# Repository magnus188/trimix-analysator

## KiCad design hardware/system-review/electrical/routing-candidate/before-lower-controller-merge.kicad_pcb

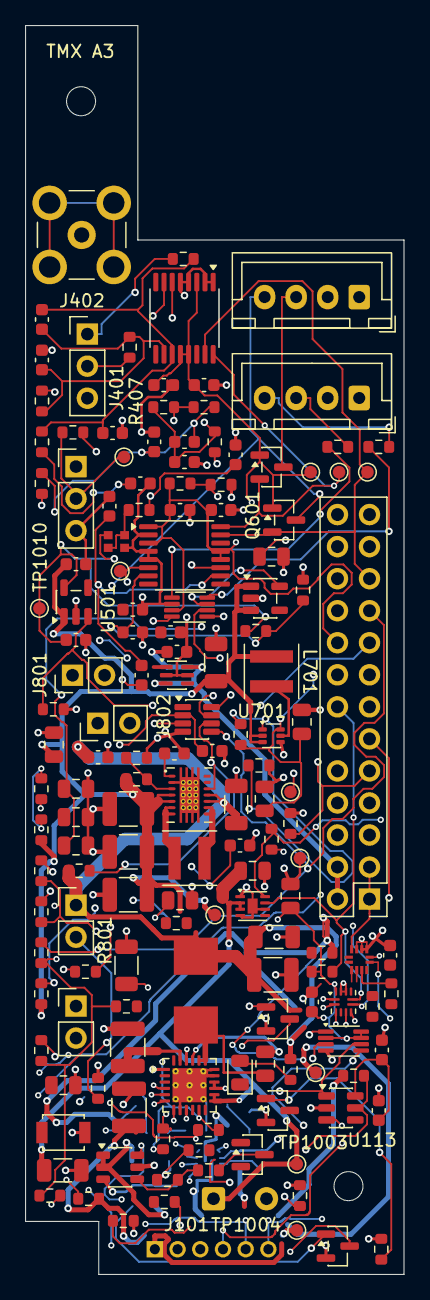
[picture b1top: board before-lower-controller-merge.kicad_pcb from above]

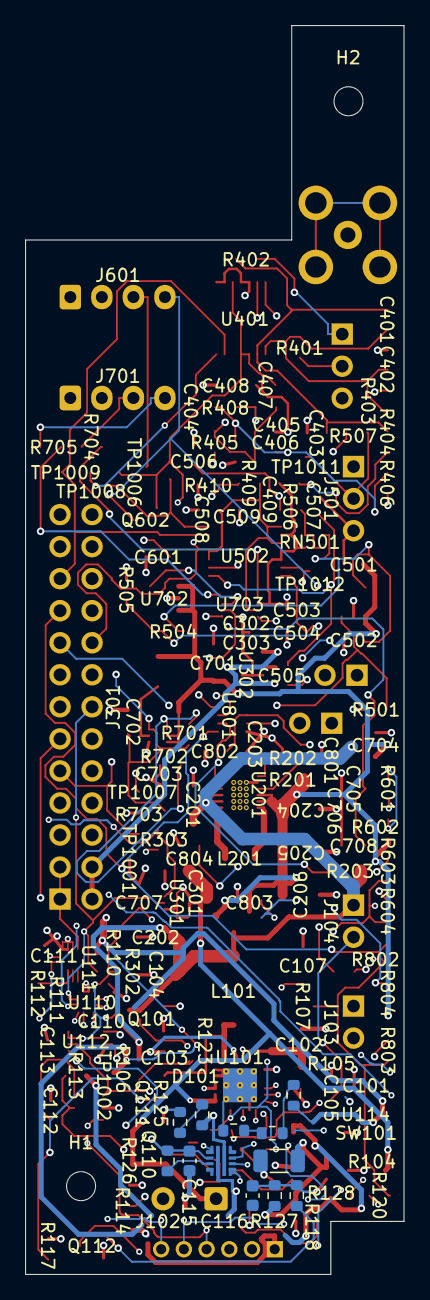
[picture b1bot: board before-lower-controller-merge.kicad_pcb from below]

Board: 4 copper layers, 30.0 x 99.0 mm, 169 parts (12 on the bottom side), 87 nets.

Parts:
C101, C601, C704, C705: 1u / 25V X7R / 10%; C_0805_2012Metric
C102, C104, C105, C204, C205, C206: 22u / 16V X7R / 20%; C_1210_3225Metric
C103: 47n / 50V X7R / 10%; C_0805_2012Metric
C106, C107, C201, C202, C701: 22u / 25V X5R / 20%; C_1206_3216Metric
C110, C111, C112, C113, C203, C407, C504, C508, C801, C802: 100n / 50V X7R / 10%; C_0603_1608Metric
C114: 4.7u / 25V X7R / 10%; C_1206_3216Metric
C115: 100n / 50V X7R; C_0603_1608Metric
C116: 3.3n / 50V C0G / 5%; C_0603_1608Metric
C301, C707, C708: 100n / 50V X7R / 10%; C_0805_2012Metric
C302, C303, C501, C502: 4.7u / 16V X5R / 10%; C_0603_1608Metric
C401, C404, C408, C409, C505, C509, C804: 1u / 16V X7R / 10%; C_0603_1608Metric
C402, C403, C405, C406, C506, C507: 10n / 50V X7R / 10%; C_0603_1608Metric
C503: 10n / 50V X7R / 10% / DNP; C_0603_1608Metric
C702, C703: 22u / 16V X5R / 20%; C_0805_2012Metric
C706: 10n / 50V X7R / 10% / DNP; C_0805_2012Metric
C803: 33n / 50V X7R / 10%; C_0805_2012Metric
D101: CHARGE (red); LED_0805_2012Metric
H1, H2: M2 NPTH 2.30; Mechanical_M2_NPTH_2.30mm
J101: USB HARNESS: 5V/GND/CC1/CC2/D+/D-; USB_Harness_6P_P1.8mm
J102: PACK PIGTAIL; Battery_Pigtail_2x22AWG_P4.2_D1.00_Pad1.85
J103: PACK NTC: 103AT-2; PinHeader_1x02_P2.54mm_Vertical
J104: ARM: OPEN; PinHeader_1x02_P2.54mm_Vertical
J301: GUITION JP1 / 2x13; Samtec_HTSW-113-07-L-D-007_P2.54mm_Key7
J401: AO2 / 3-pin cable; PinHeader_1x03_P2.54mm_Vertical
J402: SMB male-centre / Amphenol142138; SMB_Amphenol_142138
J501: MD62 cable / <=30 cm; PinHeader_1x03_P2.54mm_Vertical
J601: BME280 harness; JST_XH_B4B-XH-A_1x04_P2.50mm_Vertical
J701: ZE07-CO harness; JST_XH_B4B-XH-A_1x04_P2.50mm_Vertical
J801: POWER BUTTON / 1NO; PinHeader_1x02_P2.54mm_Vertical
J802: BUTTON LED +/-; PinHeader_1x02_P2.54mm_Vertical
L101: 1u / 74437349010; L_Wurth_74437349010_7050
L201: 1.5u / XGL4030-152MEC; L_Coilcraft_XGL4030
L701: 1u / XGL4020-102MEC; L_Coilcraft_XGL4020
Q101: 2N7002; SOT-23
Q110, Q111, Q112: DMN2056U-7; SOT-23
Q601, Q602: BSS138; SOT-23
R101: 5.23k 1%; R_0603_1608Metric
R102: 30.1k 1%; R_0603_1608Metric
R103: 300R / 1% / supported ILIM range; R_0603_1608Metric
R104, R105, R203, R501, R703, R803: 100k; R_0603_1608Metric
R106: 2.2k; R_0603_1608Metric
R107, R301, R802: 10k; R_0603_1608Metric
R110: 887k / 1%; R_0603_1608Metric
R111: 33k / 1%; R_0603_1608Metric
R112, R115, R120, R127: 10k / 1%; R_0603_1608Metric
R113: 97.6k / 0.1%; R_0603_1608Metric
R114, R409, R410, R504, R505: 10k / 0.1%; R_0603_1608Metric
R116: 1k / 0.1%; R_0603_1608Metric
R117, R118, R128: 100k / 1%; R_0603_1608Metric
R119: 19.2k / 0.1%; R_0603_1608Metric
R121: 34k / 0.1% / 10ppm; R_0603_1608Metric
R122: 649R / 0.1% / 10ppm; R_0603_1608Metric
R123: 10k / 0.1% / 10ppm; R_0603_1608Metric
R124: 21.5k / 0.1% / 25ppm; R_0603_1608Metric
R125: 10k / 0.1% / 25ppm; R_0603_1608Metric
R126: 1.65k / 0.1%; R_0603_1608Metric
R201: 1.62M 1%; R_0603_1608Metric
R202: 180k 1%; R_0603_1608Metric
R302, R303: 4.7k / FIT; R_0603_1608Metric
R401, R402, R405, R406: 100R / 0.1%; R_0603_1608Metric
R403, R404, R407, R408: 1M / 1%; R_0603_1608Metric
R506, R507: 680R / 0.1%; R_0603_1608Metric
R601: 0R / fit: 3.3 V; R_0603_1608Metric
R602: 0R / DNP: 5 V option; R_0603_1608Metric
R603, R604: 4.7k / DNP; R_0603_1608Metric
R701: 787k / 0.1%; R_0603_1608Metric
R702: 100k / 0.1%; R_0603_1608Metric
R704, R705: 100R; R_0603_1608Metric
R801: 5.1k; R_0603_1608Metric
R804: 1k / DNP; R_0603_1608Metric
RN501: 2x2k / 1:1 matched; Vishay_ACAS0606_AT_IEC
SW101: BQ service wake / B3U-1000P; SW_SPST_B3U-1000P
TP1001: GND; TestPoint_Pad_D1.0mm
TP1002: USB_5V; TestPoint_Pad_D1.0mm
TP1003: PACK_P; TestPoint_Pad_D1.0mm
TP1004: VSYS; TestPoint_Pad_D1.0mm
TP1005: VOUT_5V; TestPoint_Pad_D1.0mm
TP1006: HOST_3V3; TestPoint_Pad_D1.0mm
TP1007: POWER_EN; TestPoint_Pad_D1.0mm
TP1008: I2C_SCL; TestPoint_Pad_D1.0mm
TP1009: I2C_SDA; TestPoint_Pad_D1.0mm
TP1010: HE_3V0; TestPoint_Pad_D1.0mm
TP1011: HE_SENSE; TestPoint_Pad_D1.0mm
TP1012: O2_VMID; TestPoint_Pad_D1.0mm
U101: BQ25895RTWR; Texas_RTW_WQFN-24-1EP_4x4mm_P0.5mm_EP2.7x2.7mm_ThermalVias
U110: TUSB320LAIRWBR; Texas_X2QFN-12_1.6x1.6mm_P0.4mm
U111: PI3USB9201ZTAEX; PI3USB9201_UQFN2020_12_TypeC
U112: SN74AUP1G74DCUR; VSSOP-8_2.3x2mm_P0.5mm
U113: TPS3808G01DBVR; SOT-23-6
U114: TPS22950CQDDCRQ1; TI_DDC0006A
U115: TPS259470ARPWR; TI_RPW0010A
U201: TPS63020DSJR; TI_DSJ_14
U301: MAX17048G+; TDFN-8-1EP_2x2mm_P0.5mm_EP0.8x1.2mm
U302: LM66100DCKR; SOT-363_SC-70-6
U401, U502: ADS122C04IPWR; TSSOP-16_4.4x5mm_P0.65mm
U501, U702: TPS7A2030PDBVR; SOT-23-5
U701: TPS61023DRLR; SOT-563
U703: TXU0202DCUR; TI_DCU8_CompactSilk
U801: LTC2954CTS8-1; TSOT-23-8

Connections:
/01 CHARGING + BATTERY/BQ_BTST: C103.2, U101.21 (BTST)
/01 CHARGING + BATTERY/BQ_PMID: C102.1, U101.23 (PMID)
/01 CHARGING + BATTERY/BQ_QON_N: SW101.1, U101.12 (~QON)
/01 CHARGING + BATTERY/BQ_REGN: C107.1, R101.1, U101.22 (REGN)
/01 CHARGING + BATTERY/BQ_SW: C103.1, L101.1, U101.19 (SW), U101.20 (SW)
/01 CHARGING + BATTERY/CHG_CE_N: Q101.3 (D), R104.2, U101.9 (~CE)
/01 CHARGING + BATTERY/CHG_STAT_N: D101.1 (K), U101.4 (STAT)
/01 CHARGING + BATTERY/PACK_TS: J103.1, R101.2, R102.1, U101.11 (TS)
/02 SWITCHED 5 V/TPS_FB: R201.2, R202.1, U201.3 (FB)
/02 SWITCHED 5 V/TPS_VINA: C203.1, U201.1 (VINA)
BME_SCL: J601.3 (SCL), Q601.3 (D), R603.2
BME_SDA: J601.4 (SDA), Q602.3 (D), R604.2
BME_VIN: C601.1, J601.1 (VIN), R601.2, R602.2, R603.1, R604.1
BQ_ILIM: R103.1, U101.10 (ILIM)
BUTTON_LED_A: J802.1, R804.2
CHARGE_ARM: J104.2 (B), Q101.1 (G), R105.1
CHG_INT_N: J301.13, Q112.3 (D), R107.2, U101.7 (~INT)
CO_5V28: C702.1, C703.1, J701.1 (5.28V), R701.1, U701.6 (VOUT)
CO_FB: R701.2, R702.1, U701.1 (FB)
CO_LOGIC_3V0: C705.1, C708.1, U702.5 (OUT), U703.7 (VCCB)
CO_RX_3V0: R705.1, U703.8 (B1Y)
CO_RX_CABLE: J701.4 (CO_RX), R705.2
CO_SW: L701.2, U701.5 (SW)
CO_TX_3V0: R704.1, U703.1 (B2)
CO_TX_CABLE: J701.3 (CO_TX), R704.2
CO_UART_EN: J301.9, R703.1, U703.6 (OE)
CO_UART_RX: J301.10, U703.4 (A2Y)
CO_UART_TX: J301.12, U703.5 (A1)
GAUGE_ALERT_N: R301.2, U301.5 (ALRT)
GND: C101.2, C102.2, C104.2, C105.2, C106.2, C107.2, C110.2, C111.2, C112.2, C113.2, C114.2, C115.2, C116.2, C201.2, C202.2, C203.2, C204.2, C205.2, C206.2, C301.2, C302.2, C303.2, C402.2, C403.2, C405.2, C406.2, C407.2, C408.2, C409.2, C501.2, C502.2, C503.2, C504.2, C506.2, C507.2, C508.2, C509.2, C601.2, C701.2, C702.2, C703.2, C704.2, C705.2, C706.2, C707.2, C708.2, C801.2, C802.2, C803.2, C804.2, J101.2, J102.2, J103.2, J301.5, J301.6, J301.16, J501.3, J601.2 (GND), J701.2 (GND), J801.2, J802.2, Q101.2 (S), Q111.2 (S), Q112.2 (S), R102.2, R103.2, R105.2, R114.2, R117.2, R118.2, R119.2, R123.2, R125.2, R126.2, R127.2, R128.2, R202.2, R410.2, R501.2, R505.2, R702.2, R703.2, RN501.3 (R2.2), SW101.2, TP1001.1 (1_1), U101.8 (OTG), U101.17 (PGND), U101.18 (PGND), U101.25 (PGND), U110.3 (PORT), U110.5 (ADDR), U110.10 (GND), U110.11 (EN_N), U111.9 (GND), U111.10 (ADDR), U111.11 (ENB), U112.4 (GND), U113.2 (GND), U114.3 (GND), U115.8 (GND), U201.2 (GND), U201.15 (PGND/EP), U301.1 (CTG), U301.4 (GND), U301.6 (QSTRT), U301.9 (EP), U302.2 (GND), U302.5 (ST), U401.1 (A0), U401.2 (A1), U401.4 (DGND), U401.5 (AVSS), U501.2 (GND), U502.2 (A1), U502.4 (DGND), U502.5 (AVSS), U701.4 (GND), U702.2 (GND), U703.2 (GND), U801.4 (GND)
HE_3V0: C502.1, J501.1, R504.1, RN501.1 (R1.1), TP1010.1 (1_1), U501.5 (OUT)
HE_AIN_N: C505.2, C507.1, R507.2, U502.10 (AIN1)
HE_AIN_P: C505.1, C506.1, R506.2, U502.11 (AIN0)
HE_ENABLE: J301.17, R501.1, U501.3 (EN)
HE_EXC_DIV: C504.1, R504.2, R505.1, U502.7 (AIN2)
HE_REF: R506.1, RN501.2 (R2.1), RN501.4 (R1.2)
HE_SENSE: J501.2, R507.1, TP1011.1 (1_1)
HOST_3V3: C110.1, C111.1, C112.1, C113.1, C407.1, C408.1, C508.1, C509.1, C707.1, J301.1, J301.3, J301.18, Q601.1 (G), Q602.1 (G), R107.1, R111.1, R112.1, R115.1, R120.1, R301.1, R302.1, R303.1, R409.1, R601.1, R802.1, R803.1, TP1006.1 (1_1), U110.12 (VDD), U111.12 (VDD), U112.2 (D), U112.7 (PRE_N), U112.8 (VCC), U113.6 (VDD), U401.3 (~RESET), U401.12 (AVDD), U401.13 (DVDD), U502.1 (A0), U502.3 (~RESET), U502.12 (AVDD), U502.13 (DVDD), U703.3 (VCCA)
HOST_5V: C303.1, J301.2, J301.4, U302.3 (CE), U302.6 (VOUT)
I2C_SCL: J301.14, Q601.2 (S), R302.2, TP1008.1 (1_1), U101.5 (SCL), U110.8 (SCL), U111.3 (SCL), U301.7 (SCL), U401.16 (SCL), U502.16 (SCL)
I2C_SDA: J301.21, Q602.2 (S), R303.2, TP1009.1 (1_1), U101.6 (SDA), U110.7 (SDA), U111.4 (SDA), U301.8 (SDA), U401.15 (SDA), U502.15 (SDA)
unnamed: D101.2 (A), R106.1
unnamed: J801.1, R801.1
unnamed: L201.1, U201.8 (L1), U201.9 (L1)
unnamed: L201.2, U201.6 (L2), U201.7 (L2)
unnamed: C803.1, U801.3 (ONT)
unnamed: C804.1, U801.7 (PDT)
O2_A_AIN_N: C401.1, C402.1, R401.2, R403.1, U401.10 (AIN1)
O2_A_AIN_P: C401.2, C403.1, R402.2, R404.2, U401.11 (AIN0)
O2_A_RAW_N: J401.2, R401.1
O2_A_RAW_P: J401.1, R402.1
O2_B_AIN_N: C404.1, C405.1, R405.2, R407.1, U401.6 (AIN3)
O2_B_AIN_P: C404.2, C406.1, R406.2, R408.2, U401.7 (AIN2)
O2_B_RAW_N: J402.2 (Ext), R405.1
O2_B_RAW_P: J402.1 (In), R406.1
O2_VMID: C409.1, R403.2, R404.1, R407.2, R408.1, R409.2, R410.1, TP1012.1 (1_1), U502.6 (AIN3)
PACK_P: C106.1, C301.1, J102.1, TP1003.1 (1_1), U101.13 (BAT), U101.14 (BAT), U301.2 (CELL), U301.3 (VDD)
PB_FILTERED_N: C802.1, R801.2, U801.2 (~PB)
POWER_EN: R203.2, TP1007.1 (1_1), U201.12 (EN), U801.6 (EN)
POWER_INT_N: J301.19, R802.2, U801.5 (~INT)
POWER_KILL_N: J301.8, R803.2, U801.8 (~KILL)
USB_5V: C115.1, J101.1, R110.1, R121.1, R124.1, TP1002.1 (1_1), U115.5 (IN)
USB_BC_INT_N: R112.2, U111.5 (INTB)
USB_CC1: J101.3, U110.1 (CC1)
USB_CC2: J101.4, U110.2 (CC2)
USB_CC_INT_N: R111.2, U110.6 (INT_N), U113.3 (MR), U115.3 (AUXOFF)
USB_CHG_5V: C101.1, U101.1 (VBUS), U114.5 (VOUT)
USB_D_M: J101.6, U111.7 (D-)
USB_D_P: J101.5, U111.8 (D+)
USB_ILIM_AUTH: J301.11, Q111.1 (G), R117.1, U112.1 (CLK)
USB_ILIM_BRANCH: Q110.3 (D), R116.2
USB_ILIM_SERIES: Q110.2 (S), Q111.3 (D)
USB_LIMIT_FAULT_N: R120.2, U114.6 (FLT)
USB_LIMIT_SET: R116.1, R119.1, U114.4 (ILIM)
USB_OVP_5V: C114.1, R113.1, R127.1, U114.1 (ON), U114.2 (VIN), U115.6 (OUT)
USB_OVP_DVDT: C116.1, U115.7 (DVDT)
USB_OVP_ILM: R126.1, U115.9 (ILM)
USB_OVP_SET: R122.2, R123.1, U115.2 (OVLO)
USB_OVP_UPPER: R121.2, R122.1
USB_OVP_UVLO: R124.2, R125.1, U115.1 (EN/UVLO)
USB_PERMISSION_CLR_N: R115.2, U112.6 (CLR_N), U113.1 (RESET)
USB_PERMISSION_Q: Q110.1 (G), R118.1, U112.5 (Q)
USB_PERMISSION_Q_N: Q112.1 (G), R128.1, U112.3 (Q_N)
USB_VBUS_DET: R110.2, U110.4 (VBUS_DET)
USB_VBUS_SENSE: R113.2, R114.1, U113.5 (SENSE)
VOUT_5V: C204.1, C205.1, C206.1, C302.1, C501.1, C701.1, C704.1, L701.1, R201.1, R602.1, R804.1, TP1005.1 (1_1), U201.4 (VOUT), U201.5 (VOUT), U302.1 (VIN), U501.1 (IN), U701.2 (EN), U701.3 (VIN), U702.1 (IN), U702.3 (EN)
VSYS: C104.1, C105.1, C201.1, C202.1, C801.1, J104.1 (A), L101.2, R104.1, R106.2, R203.1, TP1004.1 (1_1), U101.15 (SYS), U101.16 (SYS), U201.10 (VIN), U201.11 (VIN), U201.13 (PS/SYNC), U801.1 (VIN)

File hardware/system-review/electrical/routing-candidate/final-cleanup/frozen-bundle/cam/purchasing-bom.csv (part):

Reference,Value,Manufacturer,MPN,Quantity,Population_quantity,Category,Footprint,Side,PCB_X_mm,PCB_Y_mm,Rotation_deg,Assembly_note,Native_exclude_from_BOM,Native_exclude_from_CPL
C101,1u / 16V X7R / 10%,KEMET / YAGEO,C0603C105K4RACTU,1,1,manual,C_0603_1608Metric,top,8.3,82.3,180.0,"manual assembly after factory inspection, using iron/hot air and microscope",False,False
C102,22u / 16V X7R / 20%,TDK,C3225X7R1C226M250AC,1,1,manual,C_1210_3225Metric,top,8.1,79.1,90.0,"manual assembly after factory inspection, using iron/hot air and microscope",False,False
C103,47n / 50V X7R / 10%,KEMET / YAGEO,C0805C473K5RACTU,1,1,manual,C_0805_2012Metric,top,19.0,82.3,90.0,"manual assembly after factory inspection, using iron/hot air and microscope",False,False
C104,22u / 16V X7R / 20%,TDK,C3225X7R1C226M250AC,1,1,manual,C_1210_3225Metric,top,19.6,75.25,0.0,"manual assembly after factory inspection, using iron/hot air and microscope",False,False
C105,22u / 16V X7R / 20%,TDK,C3225X7R1C226M250AC,1,1,manual,C_1210_3225Metric,top,8.199999,85.75,90.0,"manual assembly after factory inspection, using iron/hot air and microscope",False,False
C106,22u / 25V X5R / 20%,TDK,C3216X5R1E226M160AB,1,1,manual,C_1206_3216Metric,top,2.95,90.75,0.0,"manual assembly after factory inspection, using iron/hot air and microscope",False,False
C107,22u / 25V X5R / 20%,TDK,C3216X5R1E226M160AB,1,1,manual,C_1206_3216Metric,top,8.0,74.5,90.0,"manual assembly after factory inspection, using iron/hot air and microscope",False,False
C108,4.7u / 16V X5R / 10%,TDK,C1608X5R1C475K080AC,1,1,manual,C_0603_1608Metric,top,16.9,83.1,90.0,"manual assembly after factory inspection, using iron/hot air and microscope",False,False
C110,100n / 50V X7R / 10%,TDK,C1608X7R1H104K080AA,1,1,manual,C_0603_1608Metric,top,22.7,77.4,90.0,"manual assembly after factory inspection, using iron/hot air and microscope",False,False
C111,100n / 50V X7R / 10%,TDK,C1608X7R1H104K080AA,1,1,manual,C_0603_1608Metric,top,29.025,73.1,90.0,"manual assembly after factory inspection, using iron/hot air and microscope",False,False
C112,100n / 50V X7R / 10%,TDK,C1608X7R1H104K080AA,1,1,manual,C_0603_1608Metric,top,28.0,86.0,90.0,"manual assembly after factory inspection, using iron/hot air and microscope",False,False
C113,100n / 50V X7R / 10%,TDK,C1608X7R1H104K080AA,1,1,manual,C_0603_1608Metric,top,28.25,81.2,90.0,"manual assembly after factory inspection, using iron/hot air and microscope",False,False
C114,4.7u / 25V X7R / 10%,TDK,C3216X7R1E475K160AC,1,1,manual,C_1206_3216Metric,bottom,9.9,90.0,0.0,"manual assembly after factory inspection, using iron/hot air and microscope",False,False
C115,100n / 50V X7R,TDK,C1608X7R1H104K080AA,1,1,manual,C_0603_1608Metric,bottom,12.0,92.75,-90.0,"manual assembly after factory inspection, using iron/hot air and microscope",False,False
C116,3.3n / 50V C0G / 5%,Murata,GRM1555C1H332JE01D,1,1,factory,C_0402_1005Metric,bottom,16.5,89.05,-90.0,Factory reflow for true 0402 part; 3.3nF C0G slew timing function unchanged; exact BOM/CPL quote required; quoted factory SMT placement/reflow and joint inspection required,False,False
C201,22u / 25V X5R / 20%,TDK,C3216X5R1E226M160AB,1,1,manual,C_1206_3216Metric,top,17.0,61.75,90.0,"manual assembly after factory inspection, using iron/hot air and microscope",False,False
C202,22u / 25V X5R / 20%,TDK,C3216X5R1E226M160AB,1,1,manual,C_1206_3216Metric,top,19.7,72.25,0.0,"manual assembly after factory inspection, using iron/hot air and microscope",False,False
C203,100n / 50V X7R / 10%,TDK,C1608X7R1H104K080AA,1,1,manual,C_0603_1608Metric,top,11.8,57.7,0.0,"manual assembly after factory inspection, using iron/hot air and microscope",False,False
C204,22u / 16V X7R / 20%,TDK,C3225X7R1C226M250AC,1,1,manual,C_1210_3225Metric,top,8.15,62.1,180.0,"manual assembly after factory inspection, using iron/hot air and microscope",False,False
C205,22u / 16V X7R / 20%,TDK,C3225X7R1C226M250AC,1,1,manual,C_1210_3225Metric,top,8.15,65.5,180.0,"manual assembly after factory inspection, using iron/hot air and microscope",False,False
C206,22u / 16V X7R / 20%,TDK,C3225X7R1C226M250AC,1,1,manual,C_1210_3225Metric,top,8.15,68.9,180.0,"manual assembly after factory inspection, using iron/hot air and microscope",False,False
C301,100n / 50V X7R / 10%,KEMET / YAGEO,C0805C104K5RACTU,1,1,manual,C_0805_2012Metric,top,18.0,67.0,0.0,"manual assembly after factory inspection, using iron/hot air and microscope",False,False
C302,4.7u / 16V X5R / 10%,TDK,C1608X5R1C475K080AC,1,1,manual,C_0603_1608Metric,top,11.5,48.1,0.0,"manual assembly after factory inspection, using iron/hot air and microscope",False,False
C303,4.7u / 16V X5R / 10%,TDK,C1608X5R1C475K080AC,1,1,manual,C_0603_1608Metric,top,12.0,49.65,0.0,"manual assembly after factory inspection, using iron/hot air and microscope",False,False
C401,1u / 16V X7R / 10%,KEMET / YAGEO,C0603C105K4RACTU,1,1,manual,C_0603_1608Metric,top,1.299999,23.3,90.0,"manual assembly after factory inspection, using iron/hot air and microscope",False,False
C402,10n / 50V X7R / 10%,TDK,C1608X7R1H103K080AA,1,1,manual,C_0603_1608Metric,top,1.299999,26.51,90.0,"manual assembly after factory inspection, using iron/hot air and microscope",False,False
C403,10n / 50V X7R / 10%,TDK,C1608X7R1H103K080AA,1,1,manual,C_0603_1608Metric,top,6.9,32.299999,0.0,"manual assembly after factory inspection, using iron/hot air and microscope",False,False
C404,1u / 16V X7R / 10%,KEMET / YAGEO,C0603C105K4RACTU,1,1,manual,C_0603_1608Metric,top,12.6,33.0,0.0,"manual assembly after factory inspection, using iron/hot air and microscope",False,False
C405,10n / 50V X7R / 10%,TDK,C1608X7R1H103K080AA,1,1,manual,C_0603_1608Metric,top,12.6,34.6,0.0,"manual assembly after factory inspection, using iron/hot air and microscope",False,False
C406,10n / 50V X7R / 10%,TDK,C1608X7R1H103K080AA,1,1,manual,C_0603_1608Metric,top,10.2,33.0,90.0,"manual assembly after factory inspection, using iron/hot air and microscope",False,False
C407,100n / 50V X7R / 10%,TDK,C1608X7R1H104K080AA,1,1,manual,C_0603_1608Metric,top,10.95,28.5,0.0,"manual assembly after factory inspection, using iron/hot air and microscope",False,False
C408,1u / 16V X7R / 10%,KEMET / YAGEO,C0603C105K4RACTU,1,1,manual,C_0603_1608Metric,top,14.15,28.5,0.0,"manual assembly after factory inspection, using iron/hot air and microscope",False,False
C409,1u / 16V X7R / 10%,KEMET / YAGEO,C0603C105K4RACTU,1,1,manual,C_0603_1608Metric,top,9.1,36.3,0.0,"manual assembly after factory inspection, using iron/hot air and microscope",False,False
C501,4.7u / 16V X5R / 10%,TDK,C1608X5R1C475K080AC,1,1,manual,C_0603_1608Metric,top,4.0,42.7,0.0,"manual assembly after factory inspection, using iron/hot air and microscope",False,False
C502,4.7u / 16V X5R / 10%,TDK,C1608X5R1C475K080AC,1,1,manual,C_0603_1608Metric,top,4.0,48.7,0.0,"manual assembly after factory inspection, using iron/hot air and microscope",False,False
C504,100n / 50V X7R / 10%,TDK,C1608X7R1H104K080AA,1,1,manual,C_0603_1608Metric,top,8.5,48.1,0.0,"manual assembly after factory inspection, using iron/hot air and microscope",False,False
C505,1u / 16V X7R / 10%,KEMET / YAGEO,C0603C105K4RACTU,1,1,manual,C_0603_1608Metric,top,9.2,51.5,90.0,"manual assembly after factory inspection, using iron/hot air and microscope",False,False
C506,10n / 50V X7R / 10%,TDK,C1608X7R1H103K080AA,1,1,manual,C_0603_1608Metric,top,16.649999,34.025,90.0,"manual assembly after factory inspection, using iron/hot air and microscope",False,False
C507,10n / 50V X7R / 10%,TDK,C1608X7R1H103K080AA,1,1,manual,C_0603_1608Metric,top,6.65,38.1,90.0,"manual assembly after factory inspection, using iron/hot air and microscope",False,False
C508,100n / 50V X7R / 10%,TDK,C1608X7R1H104K080AA,1,1,manual,C_0603_1608Metric,top,15.5,38.4,0.0,"manual assembly after factory inspection, using iron/hot air and microscope",False,False
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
